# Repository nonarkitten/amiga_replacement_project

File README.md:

# Amiga Replacement Project

_"To make replacements for all the custom chips of the AMIGA, useable in any real AMIGA."_

All documentation is provided for the benefit of the community and the preservation of the original Amiga.

The files herein are presented as a work-in-progress.

ReAgnus as developed by Stephen Leary the patents and any documentation included here for reference and may be considered Public Domain. I claim no licensing on any of these.

ReAgnus developed by the Buffee Project (code named Willoe) is under the <a rel="license" href="http://creativecommons.org/licenses/by-nc-sa/4.0/">Creative Commons Attribution-NonCommercial-ShareAlike 4.0 International License</a>. No part of which shall be used for any commercial gains without express and written permission from The Buffee Project.

This is an attempt to make clean Verilog sources for each chip on the Amiga. Unlike MiniMig and related implementations, this seeks to maintain perfect compatibility with the whole chip and the whole chip only to serve as a second-source to the slowly disappearing stock of Amiga chips. These will be drop-in replacements.

To view the plan of record for each chip, please visit the README.md for each project.

Much of the work is based on the excellent efforts of Dennis van Weeren and Frederic Requin (https://github.com/fredrequin).

## OCS
Our OCS goal will include a 512KB Agnus, Denise and Paula supporting basic NTSC and PAL modes. OCS should be drop-in compatible with the Amiga 1000 "skinny" Agnus as well as the early "fat" Agnus on Amiga 500 and 2000 systems. Eventually we will have a DIP 48 solution for this as well.

## ECS
Expands the chip memory to 2MB with two common pin outs that are slightly incompatible with each other. Some bugs need to be supported but the weird limitations of productivity mode do not. The PLCC socketed PCB for Agnus will present a unique engineering challenge; the other chips remain DIP 48.

## AGA-on-ECS
This provides as much AGA functionality on either OCS or ECS based systems and retains the existing pinouts (and 16-bit data bus limitation). It should be possible to implement FP/EDO memory to get 2X increase and it might be possible to extend that to a 4X improvement with faster memory. We may also simply use SDRAM (3.3V SDR) and start with the fastest memory we can to achieve this.

## Vampire AGA
We'may also add to the AGA core some of the added features of the Vampire.

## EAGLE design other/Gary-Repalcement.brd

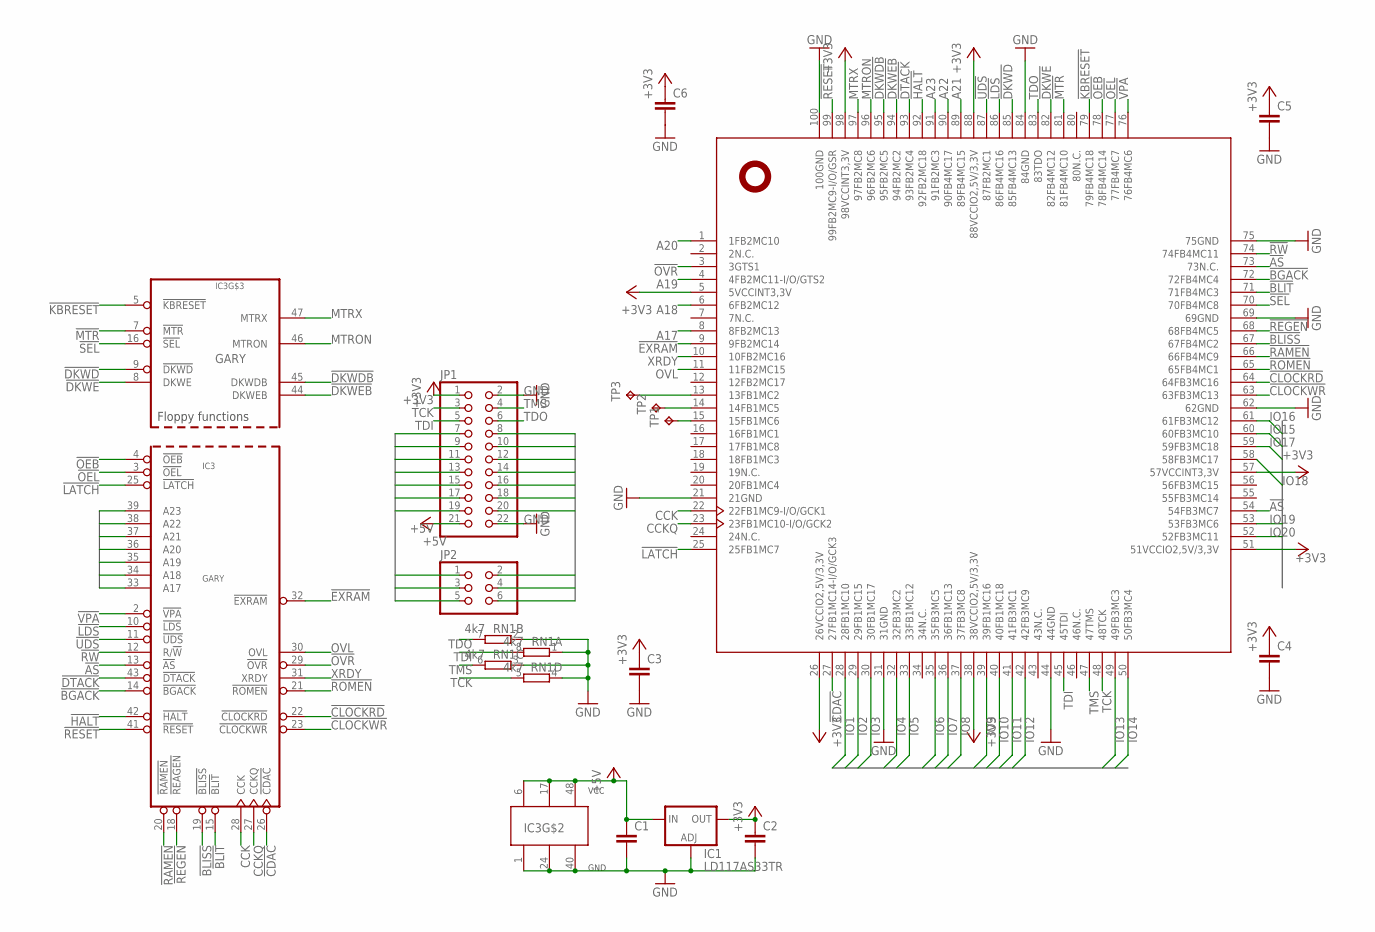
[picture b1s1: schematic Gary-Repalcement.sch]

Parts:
C1, C2: C-EUC0805K; C0805K
C3, C4, C5, C6: C-EUC0603; C0603
IC1: LD117AS33TR; SOT223
IC2: XC9572XLTQ100; TQ100
IC3: GARY_DIP-LABELS; DIP48-GARY
JP1: PINHD-2X11; 2X11
JP2: PINHD-2X3; 2X03
RN1: 4k7; 0603-ARC
TP1, TP2, TP3: TPB1,27; B1,27

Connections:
!AS: IC2.54 (54FB3MC7), IC2.73 (73N.C.), IC3.13 (!AS)
!BGACK: IC2.72 (72FB4MC4), IC3.14 (!BGACK)
!BLISS: IC2.67 (67FB4MC2), IC3.19 (!BLISS)
!BLIT: IC2.71 (71FB4MC3), IC3.15 (!BLIT)
!CDAC: IC2.27 (27FB1MC14-I/O/GCK3), IC3.26 (!CDAC)
!CLOCKRD: IC2.64 (64FB3MC16), IC3.22 (!CLOCKRD)
!CLOCKWR: IC2.63 (63FB3MC13), IC3.23 (!CLOCKWR)
!DKWD: IC2.85 (85FB4MC13), IC3.9 (!DKWD)
!DKWDB: IC2.95 (95FB2MC5), IC3.45 (DKWDB)
!DKWE: IC2.82 (82FB4MC12), IC3.8 (DKWE)
!DKWEB: IC2.94 (94FB2MC2), IC3.44 (DKWEB)
!DTACK: IC2.93 (93FB2MC4), IC3.43 (!DTACK)
!EXRAM: IC2.9 (9FB2MC14), IC3.32 (!EXRAM)
!HALT: IC2.92 (92FB2MC18), IC3.42 (!HALT)
!KBRESET: IC2.79 (79FB4MC18), IC3.5 (!KBRESET)
!LATCH: IC2.25 (25FB1MC7), IC3.25 (!LATCH)
!LDS: IC2.86 (86FB4MC16), IC3.10 (!LDS)
!MTR: IC2.81 (81FB4MC10), IC3.7 (!MTR)
!OEB: IC2.78 (78FB4MC14), IC3.4 (!OEB)
!OEL: IC2.77 (77FB4MC7), IC3.3 (!OEL)
!OVR: IC2.3 (3GTS1), IC3.29 (!OVR)
!RAMEN: IC2.66 (66FB4MC9), IC3.20 (!RAMEN)
!REGEN: IC2.68 (68FB4MC5), IC3.18 (!REAGEN)
!RESET: IC2.99 (99FB2MC9-I/O/GSR), IC3.41 (!RESET)
!ROMEN: IC2.65 (65FB4MC1), IC3.21 (!ROMEN)
!RW: IC2.74 (74FB4MC11), IC3.12 (R/!W!)
!SEL: IC2.70 (70FB4MC8), IC3.16 (!SEL)
!UDS: IC2.87 (87FB2MC1), IC3.11 (!UDS)
!VPA: IC2.76 (76FB4MC6), IC3.2 (!VPA)
+3V3: C2.1, C3.1, C4.1, C5.1, C6.1, IC1.2 (OUT), IC1.4 (OUT), IC2.5 (5VCCINT3,3V), IC2.26 (26VCCIO2,5V/3,3V), IC2.38 (38VCCIO2,5V/3,3V), IC2.51 (51VCCIO2,5V/3,3V), IC2.57 (57VCCINT3,3V), IC2.88 (88VCCIO2,5V/3,3V), IC2.98 (98VCCINT3,3V), JP1.1
+5V: C1.1, IC1.3 (IN), IC3.6 (VCC), IC3.17 (VCC), IC3.48 (VCC), JP1.21
A17: IC2.8 (8FB2MC13), IC3.33 (A17)
A18: IC2.6 (6FB2MC12), IC3.34 (A18)
A19: IC2.4 (4FB2MC11-I/O/GTS2), IC3.35 (A19)
A20: IC2.1 (1FB2MC10), IC3.36 (A20)
A21: IC2.89 (89FB4MC15), IC3.37 (A21)
A22: IC2.90 (90FB4MC17), IC3.38 (A22)
A23: IC2.91 (91FB2MC3), IC3.39 (A23)
CCK: IC2.22 (22FB1MC9-I/O/GCK1), IC3.28 (CCK)
CCKQ: IC2.23 (23FB1MC10-I/O/GCK2), IC3.27 (CCKQ)
GND: C1.2, C2.2, C3.2, C4.2, C5.2, C6.2, IC1.1 (ADJ), IC2.21 (21GND), IC2.31 (31GND), IC2.44 (44GND), IC2.62 (62GND), IC2.69 (69GND), IC2.75 (75GND), IC2.84 (84GND), IC2.100 (100GND), IC3.1 (GND), IC3.24 (GND), IC3.40 (GND), JP1.2, JP1.22, RN1.1, RN1.2 (1), RN1.3 (1), RN1.4 (1)
IO1: IC2.28 (28FB1MC10), JP1.19
IO2: IC2.29 (29FB1MC15), JP1.20
IO3: IC2.30 (30FB1MC17), JP1.17
IO4: IC2.32 (32FB3MC2), JP1.18
IO5: IC2.33 (33FB1MC12), JP1.15
IO6: IC2.35 (35FB3MC5), JP1.16
IO7: IC2.36 (36FB1MC13), JP1.13
IO8: IC2.37 (37FB3MC8), JP1.14
IO9: IC2.39 (39FB1MC16), JP1.11
IO10: IC2.40 (40FB1MC18), JP1.12
IO11: IC2.41 (41FB3MC1), JP1.9
IO12: IC2.42 (42FB3MC9), JP1.10
IO13: IC2.49 (49FB3MC3), JP1.7
IO14: IC2.50 (50FB3MC4), JP1.8
IO15: IC2.60 (60FB3MC10), JP2.2
IO16: IC2.61 (61FB3MC12), JP2.1
IO17: IC2.59 (59FB3MC18), JP2.4
IO18: IC2.58 (58FB3MC17), JP2.3
IO19: IC2.53 (53FB3MC6), JP2.6
IO20: IC2.52 (52FB3MC11), JP2.5
MTRON: IC2.96 (96FB2MC6), IC3.46 (MTRON)
MTRX: IC2.97 (97FB2MC8), IC3.47 (MTRX)
unnamed: IC2.15 (15FB1MC6), TP1.TP
unnamed: IC2.14 (14FB1MC5), TP2.TP
unnamed: IC2.13 (13FB1MC2), TP3.TP
OVL: IC2.11 (11FB2MC15), IC3.30 (OVL)
TCK: IC2.48 (48TCK), JP1.3, RN1.5 (2)
TDI: IC2.45 (45TDI), JP1.5, RN1.8 (2)
TDO: IC2.83 (83TDO), JP1.6, RN1.7 (2)
TMS: IC2.47 (47TMS), JP1.4, RN1.6 (2)
XRDY: IC2.10 (10FB2MC16), IC3.31 (XRDY)

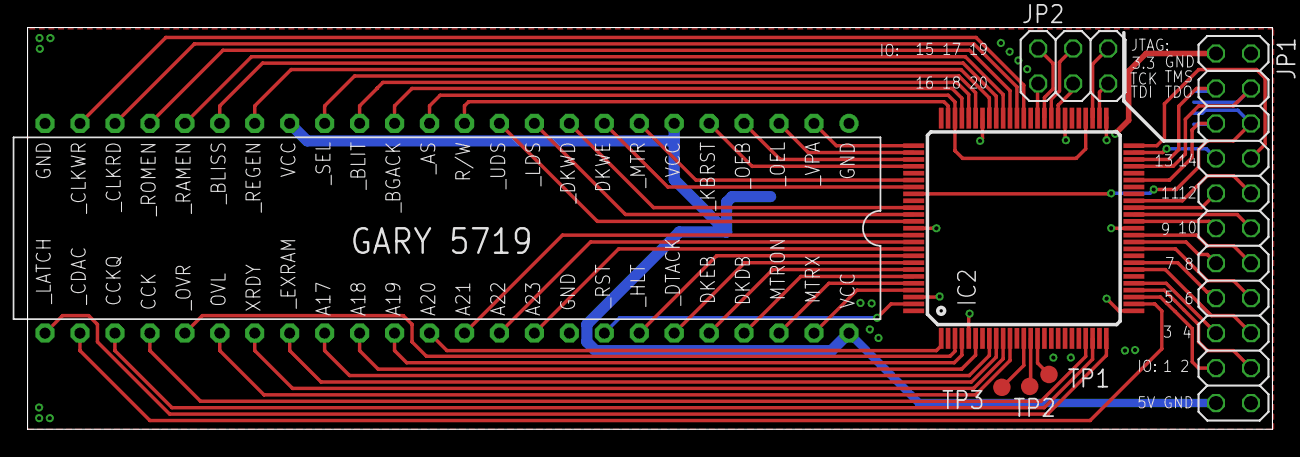
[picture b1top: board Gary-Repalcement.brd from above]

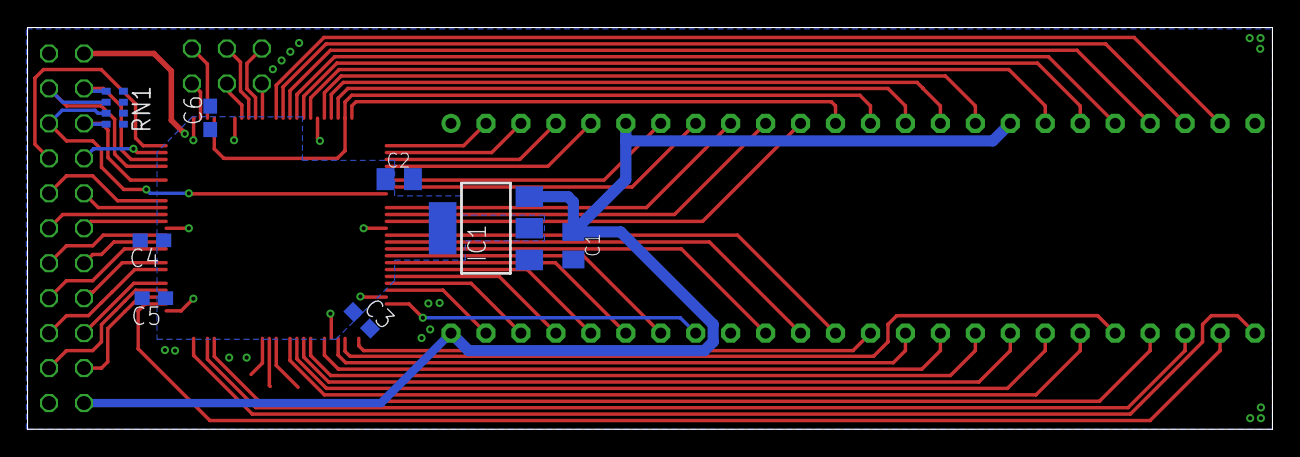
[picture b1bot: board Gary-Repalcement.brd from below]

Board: 2 copper layers, 90.5 x 29.2 mm, 15 parts (8 on the bottom side), 72 nets.

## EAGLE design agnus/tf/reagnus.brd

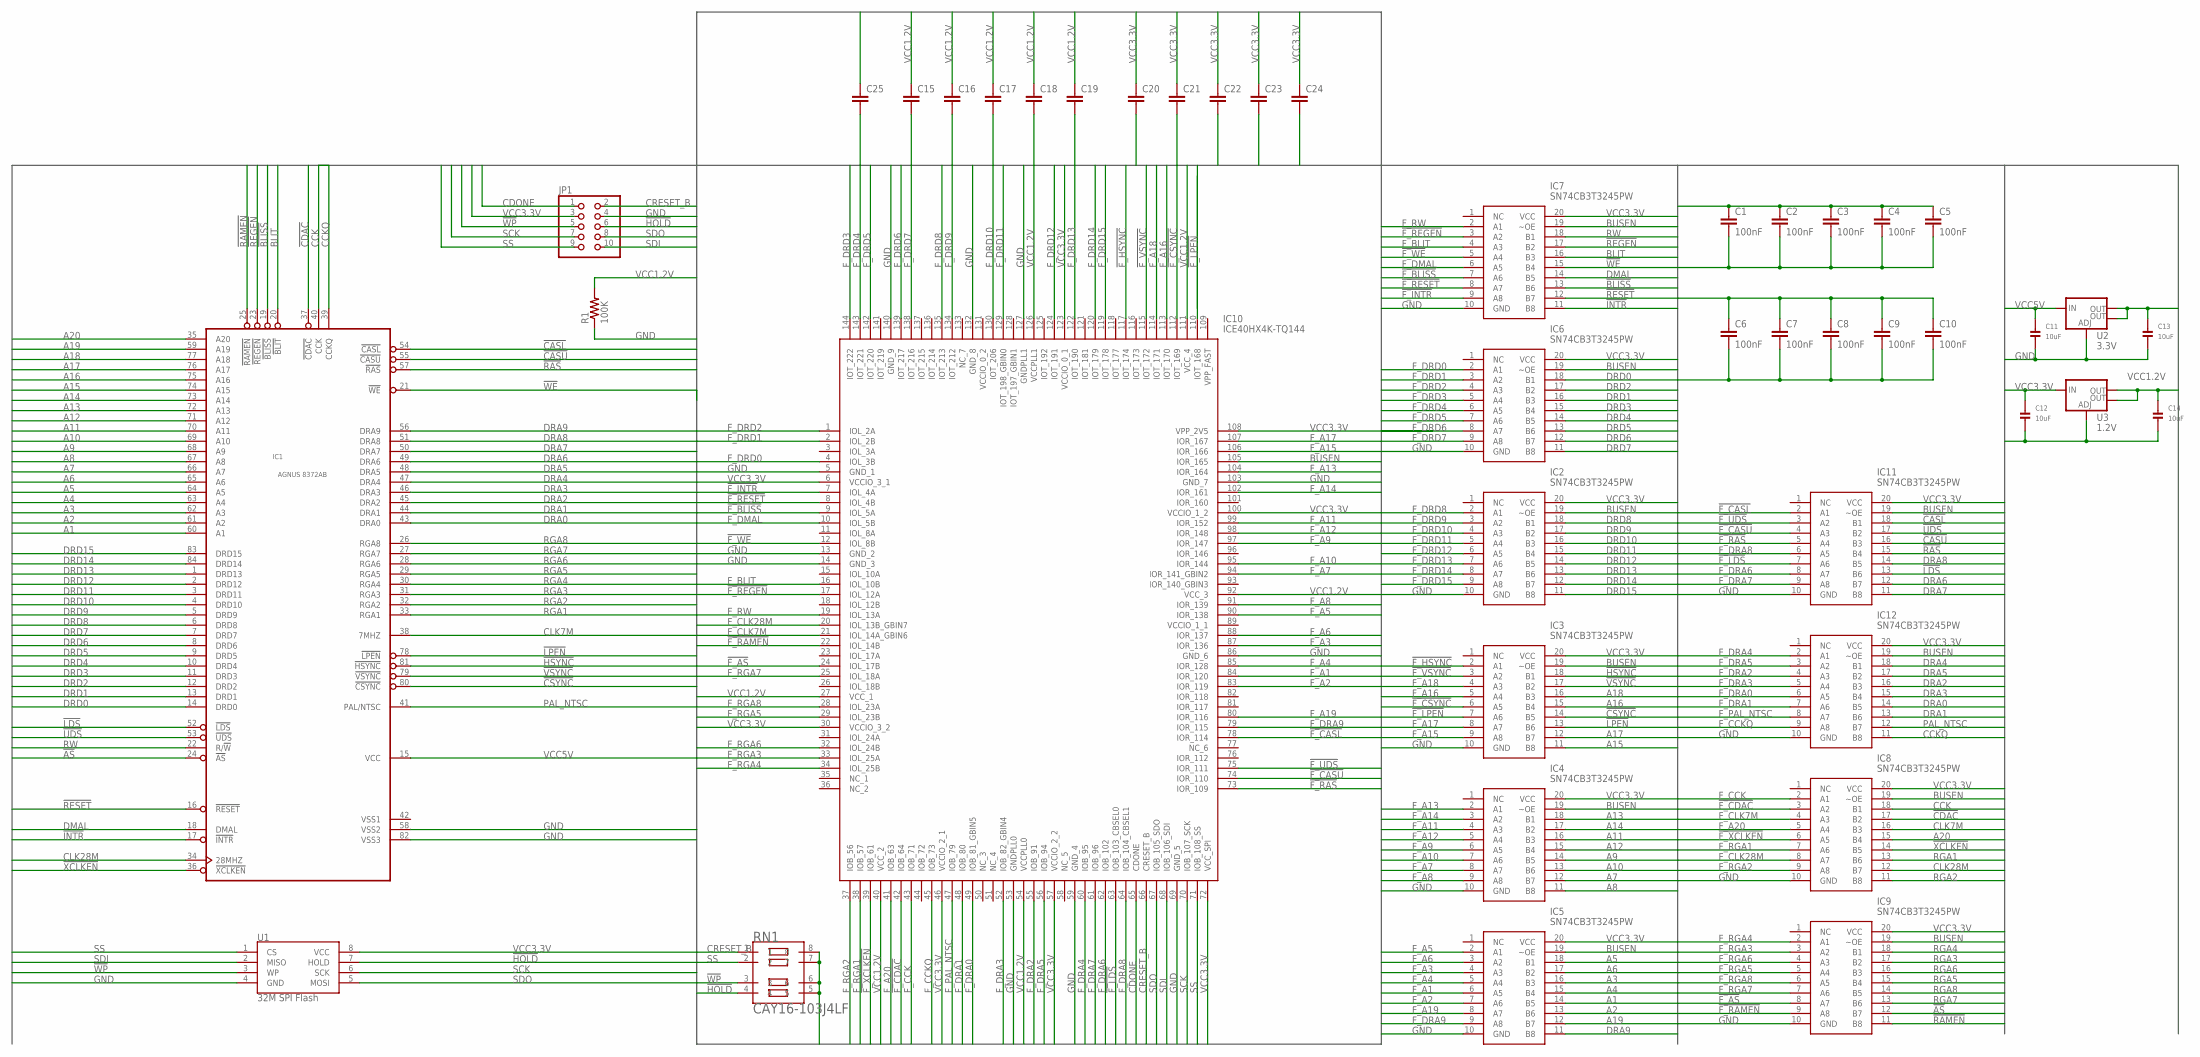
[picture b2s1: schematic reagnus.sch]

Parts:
C1, C2, C3, C4, C5, C6, C7, C8, C9, C10: 100nF; C0805K
C11, C12, C13, C14: 10uF; 1206
C15, C16, C17, C18, C19, C20, C21, C22, C23, C24, C25: C-EUC0805K; C0805K
IC1: AGNUS_8372AB_THT; PLCC84_T
IC2, IC3, IC4, IC5, IC6, IC7, IC8, IC9, IC11, IC12: SN74CB3T3245PW; SOP65P640X120-20N
IC10: ICE40HX4K-TQ144; QFP50P2200X2200X160-144N
JP1: HEADER-2X5; 2X05
R1: 100K; R0805
RN1: CAY16-103J4LF; RESCAXE80P320X160-8N
U1: 32M SPI Flash; SO08
U2: 3.3V; SOT223
U3: 1.2V; SOT223

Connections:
!AS: IC1.24 (!AS), IC9.12 (B7)
!BLISS: IC1.19 (!BLISS), IC7.13 (B6)
!CASL: IC1.54 (!CASL), IC11.18 (B1)
!CASU: IC1.55 (!CASU), IC11.16 (B3)
!CDAC: IC1.37 (!CDAC), IC8.17 (B2)
!CSYNC: IC1.80 (!CSYNC), IC3.14 (B5)
!F_AS: IC9.8 (A7), IC10.24 (IOL_17B)
!F_BLISS: IC7.7 (A6), IC10.9 (IOL_5A)
!F_CASL: IC10.78 (IOR_114), IC11.2 (A1)
!F_CASU: IC10.74 (IOR_110), IC11.4 (A3)
!F_CDAC: IC8.3 (A2), IC10.42 (IOB_64)
!F_CSYNC: IC3.6 (A5), IC10.112 (IOT_169)
!F_HSYNC: IC3.2 (A1), IC10.117 (IOT_174)
!F_INTR: IC7.9 (A8), IC10.7 (IOL_4A)
!F_LDS: IC10.63 (IOB_103_CBSEL0), IC11.7 (A6)
!F_LPEN: IC3.7 (A6), IC10.110 (IOT_168)
!F_RAMEN: IC9.9 (A8), IC10.22 (IOL_14B)
!F_RAS: IC10.73 (IOR_109), IC11.5 (A4)
!F_REGEN: IC7.3 (A2), IC10.17 (IOL_12A)
!F_RESET: IC7.8 (A7), IC10.8 (IOL_4B)
!F_UDS: IC10.75 (IOR_111), IC11.3 (A2)
!F_VSYNC: IC3.3 (A2), IC10.115 (IOT_172)
!F_WE: IC7.5 (A4), IC10.12 (IOL_8B)
!F_XCLKEN: IC8.6 (A5), IC10.39 (IOB_61)
!HOLD: JP1.6, RN1.4, U1.7 (HOLD)
!HSYNC: IC1.81 (!HSYNC), IC3.18 (B1)
!INTR: IC1.17 (!INTR), IC7.11 (B8)
!LDS: IC1.52 (!LDS), IC11.13 (B6)
!LPEN: IC1.78 (!LPEN), IC3.13 (B6)
!RAMEN: IC1.25 (!RAMEN), IC9.11 (B8)
!RAS: IC1.57 (!RAS), IC11.15 (B4)
!REGEN: IC1.23 (!REGEN), IC7.17 (B2)
!RESET: IC1.16 (!RESET), IC7.12 (B7)
!UDS: IC1.53 (!UDS), IC11.17 (B2)
!VSYNC: IC1.79 (!VSYNC), IC3.17 (B2)
!WE: IC1.21 (!WE), IC7.15 (B4)
!WP: JP1.5, RN1.3, U1.3 (WP)
!XCLKEN: IC1.36 (!XCLKEN), IC8.14 (B5)
A1: IC1.60 (A1), IC5.14 (B5)
A2: IC1.61 (A2), IC5.13 (B6)
A3: IC1.62 (A3), IC5.16 (B3)
A4: IC1.63 (A4), IC5.15 (B4)
A5: IC1.64 (A5), IC5.18 (B1)
A6: IC1.65 (A6), IC5.17 (B2)
A7: IC1.66 (A7), IC4.12 (B7)
A8: IC1.67 (A8), IC4.11 (B8)
A9: IC1.68 (A9), IC4.14 (B5)
A10: IC1.69 (A10), IC4.13 (B6)
A11: IC1.70 (A11), IC4.16 (B3)
A12: IC1.71 (A12), IC4.15 (B4)
A13: IC1.72 (A13), IC4.18 (B1)
A14: IC1.73 (A14), IC4.17 (B2)
A15: IC1.74 (A15), IC3.11 (B8)
A16: IC1.75 (A16), IC3.15 (B4)
A17: IC1.76 (A17), IC3.12 (B7)
A18: IC1.77 (A18), IC3.16 (B3)
A19: IC1.59 (A19), IC5.12 (B7)
A20: IC1.35 (A20), IC8.15 (B4)
BLIT: IC1.20 (!BLIT), IC7.16 (B3)
BUSEN: IC2.19 (~OE), IC3.19 (~OE), IC4.19 (~OE), IC5.19 (~OE), IC6.19 (~OE), IC7.19 (~OE), IC8.19 (~OE), IC9.19 (~OE), IC10.105 (IOR_165), IC11.19 (~OE), IC12.19 (~OE)
CCK: IC1.40 (CCK), IC8.18 (B1)
CCKQ: IC1.39 (CCKQ), IC12.11 (B8)
CDONE: IC10.65 (CDONE), JP1.1
CLK7M: IC1.38 (7MHZ), IC8.16 (B3)
CLK28M: IC1.34 (28MHZ), IC8.12 (B7)
CRESET_B: IC10.66 (CRESET_B), JP1.2, RN1.1
DMAL: IC1.18 (DMAL), IC7.14 (B5)
DRA0: IC1.43 (DRA0), IC12.14 (B5)
DRA1: IC1.44 (DRA1), IC12.13 (B6)
DRA2: IC1.45 (DRA2), IC12.16 (B3)
DRA3: IC1.46 (DRA3), IC12.15 (B4)
DRA4: IC1.47 (DRA4), IC12.18 (B1)
DRA5: IC1.48 (DRA5), IC12.17 (B2)
DRA6: IC1.49 (DRA6), IC11.12 (B7)
DRA7: IC1.50 (DRA7), IC11.11 (B8)
DRA8: IC1.51 (DRA8), IC11.14 (B5)
DRA9: IC1.56 (DRA9), IC5.11 (B8)
DRD0: IC1.14 (DRD0), IC6.18 (B1)
DRD1: IC1.13 (DRD1), IC6.16 (B3)
DRD2: IC1.12 (DRD2), IC6.17 (B2)
DRD3: IC1.11 (DRD3), IC6.15 (B4)
DRD4: IC1.10 (DRD4), IC6.14 (B5)
DRD5: IC1.9 (DRD5), IC6.13 (B6)
DRD6: IC1.8 (DRD6), IC6.12 (B7)
DRD7: IC1.7 (DRD7), IC6.11 (B8)
DRD8: IC1.6 (DRD8), IC2.18 (B1)
DRD9: IC1.5 (DRD9), IC2.17 (B2)
DRD10: IC1.4 (DRD10), IC2.16 (B3)
DRD11: IC1.3 (DRD11), IC2.15 (B4)
DRD12: IC1.2 (DRD12), IC2.14 (B5)
DRD13: IC1.1 (DRD13), IC2.13 (B6)
DRD14: IC1.84 (DRD14), IC2.12 (B7)
DRD15: IC1.83 (DRD15), IC2.11 (B8)
F_A1: IC5.6 (A5), IC10.84 (IOR_120)
F_A2: IC5.7 (A6), IC10.83 (IOR_119)
F_A3: IC5.4 (A3), IC10.87 (IOR_136)
F_A4: IC5.5 (A4), IC10.85 (IOR_128)
F_A5: IC5.2 (A1), IC10.90 (IOR_138)
F_A6: IC5.3 (A2), IC10.88 (IOR_137)
F_A7: IC4.8 (A7), IC10.94 (IOR_141_GBIN2)
F_A8: IC4.9 (A8), IC10.91 (IOR_139)
F_A9: IC4.6 (A5), IC10.97 (IOR_147)
F_A10: IC4.7 (A6), IC10.95 (IOR_144)
F_A11: IC4.4 (A3), IC10.99 (IOR_152)
F_A12: IC4.5 (A4), IC10.98 (IOR_148)
F_A13: IC4.2 (A1), IC10.104 (IOR_164)
F_A14: IC4.3 (A2), IC10.102 (IOR_161)
F_A15: IC3.9 (A8), IC10.106 (IOR_166)
F_A16: IC3.5 (A4), IC10.113 (IOT_170)
F_A17: IC3.8 (A7), IC10.107 (IOR_167)
F_A18: IC3.4 (A3), IC10.114 (IOT_171)
F_A19: IC5.8 (A7), IC10.80 (IOR_116)
F_A20: IC8.5 (A4), IC10.41 (IOB_63)
F_BLIT: IC7.4 (A3), IC10.16 (IOL_10B)
F_CCK: IC8.2 (A1), IC10.43 (IOB_71)
F_CCKQ: IC10.45 (IOB_73), IC12.9 (A8)
F_CLK7M: IC8.4 (A3), IC10.21 (IOL_14A_GBIN6)
F_CLK28M: IC8.8 (A7), IC10.20 (IOL_13B_GBIN7)
F_DMAL: IC7.6 (A5), IC10.10 (IOL_5B)
F_DRA0: IC10.49 (IOB_81_GBIN5), IC12.6 (A5)
F_DRA1: IC10.48 (IOB_80), IC12.7 (A6)
F_DRA2: IC10.55 (IOB_91), IC12.4 (A3)
F_DRA3: IC10.52 (IOB_82_GBIN4), IC12.5 (A4)
F_DRA4: IC10.60 (IOB_95), IC12.2 (A1)
F_DRA5: IC10.56 (IOB_94), IC12.3 (A2)
F_DRA6: IC10.62 (IOB_102), IC11.8 (A7)
F_DRA7: IC10.61 (IOB_96), IC11.9 (A8)
F_DRA8: IC10.64 (IOB_104_CBSEL1), IC11.6 (A5)
F_DRA9: IC5.9 (A8), IC10.79 (IOR_115)
F_DRD0: IC6.2 (A1), IC10.4 (IOL_3B)
F_DRD1: IC6.3 (A2), IC10.2 (IOL_2B)
F_DRD2: IC6.4 (A3), IC10.1 (IOL_2A)
F_DRD3: IC6.5 (A4), IC10.144 (IOT_222)
F_DRD4: IC6.6 (A5), IC10.143 (IOT_221)
F_DRD5: IC6.7 (A6), IC10.142 (IOT_220)
F_DRD6: IC6.8 (A7), IC10.139 (IOT_217)
F_DRD7: IC6.9 (A8), IC10.138 (IOT_216)
F_DRD8: IC2.2 (A1), IC10.135 (IOT_213)
F_DRD9: IC2.3 (A2), IC10.134 (IOT_212)
F_DRD10: IC2.4 (A3), IC10.130 (IOT_206)
F_DRD11: IC2.5 (A4), IC10.129 (IOT_198_GBIN0)
F_DRD12: IC2.6 (A5), IC10.124 (IOT_191)
F_DRD13: IC2.7 (A6), IC10.122 (IOT_190)
F_DRD14: IC2.8 (A7), IC10.120 (IOT_179)
F_DRD15: IC2.9 (A8), IC10.119 (IOT_178)
F_PAL_NTSC: IC10.47 (IOB_79), IC12.8 (A7)
F_RGA1: IC8.7 (A6), IC10.38 (IOB_57)
F_RGA2: IC8.9 (A8), IC10.37 (IOB_56)
F_RGA3: IC9.3 (A2), IC10.33 (IOL_25A)
F_RGA4: IC9.2 (A1), IC10.34 (IOL_25B)
F_RGA5: IC9.5 (A4), IC10.29 (IOL_23B)
F_RGA6: IC9.4 (A3), IC10.32 (IOL_24B)
F_RGA7: IC9.7 (A6), IC10.25 (IOL_18A)
F_RGA8: IC9.6 (A5), IC10.28 (IOL_23A)
F_RW: IC7.2 (A1), IC10.19 (IOL_13A)
GND: C1.2, C2.2, C3.2, C4.2, C5.2, C6.2, C7.2, C8.2, C9.2, C10.2, C11.2, C12.2, C13.2, C14.2, C15.2, C16.2, C17.2, C18.2, C19.2, C20.2, C21.2, C22.2, C23.2, C24.2, C25.2, IC1.58 (VSS2), IC1.82 (VSS3), IC2.10 (GND), IC3.10 (GND), IC4.10 (GND), IC5.10 (GND), IC6.10 (GND), IC7.10 (GND), IC8.10 (GND), IC9.10 (GND), IC10.5 (GND_1), IC10.13 (GND_2), IC10.14 (GND_3), IC10.53 (GNDPLL0), IC10.59 (GND_4), IC10.69 (GND_5), IC10.86 (GND_6), IC10.103 (GND_7), IC10.127 (GNDPLL1), IC10.132 (GND_8), IC10.140 (GND_9), IC11.10 (GND), IC12.10 (GND), JP1.4, R1.1, U1.4 (GND), U2.1 (ADJ), U3.1 (ADJ)
PAL_NTSC: IC1.41 (PAL/NTSC), IC12.12 (B7)
RGA1: IC1.33 (RGA1), IC8.13 (B6)
RGA2: IC1.32 (RGA2), IC8.11 (B8)
RGA3: IC1.31 (RGA3), IC9.17 (B2)
RGA4: IC1.30 (RGA4), IC9.18 (B1)
RGA5: IC1.29 (RGA5), IC9.15 (B4)
RGA6: IC1.28 (RGA6), IC9.16 (B3)
RGA7: IC1.27 (RGA7), IC9.13 (B6)
RGA8: IC1.26 (RGA8), IC9.14 (B5)
RW: IC1.22 (R/!W!), IC7.18 (B1)
SCK: IC10.70 (IOB_107_SCK), JP1.7, U1.6 (SCK)
SDI: IC10.68 (IOB_106_SDI), JP1.10, U1.2 (MISO)
SDO: IC10.67 (IOB_105_SDO), JP1.8, U1.5 (MOSI)
SS: IC10.71 (IOB_108_SS), JP1.9, RN1.2, U1.1 (CS)
VCC1.2V: C14.1, C15.1, C16.1, C17.1, C18.1, C19.1, C25.1, IC10.27 (VCC_1), IC10.40 (VCC_2), IC10.54 (VCCPLL0), IC10.92 (VCC_3), IC10.111 (VCC_4), IC10.126 (VCCPLL1), R1.2, U3.2 (OUT), U3.4 (OUT)
VCC3.3V: C1.1, C2.1, C3.1, C4.1, C5.1, C6.1, C7.1, C8.1, C9.1, C10.1, C12.1, C13.1, C20.1, C21.1, C22.1, C23.1, C24.1, IC2.20 (VCC), IC3.20 (VCC), IC4.20 (VCC), IC5.20 (VCC), IC6.20 (VCC), IC7.20 (VCC), IC8.20 (VCC), IC9.20 (VCC), IC10.6 (VCCIO_3_1), IC10.30 (VCCIO_3_2), IC10.46 (VCCIO_2_1), IC10.57 (VCCIO_2_2), IC10.72 (VCC_SPI), IC10.100 (VCCIO_1_2), IC10.108 (VPP_2V5), IC10.123 (VCCIO_0_1), IC11.20 (VCC), IC12.20 (VCC), JP1.3, RN1.5, RN1.6, RN1.7, RN1.8, U1.8 (VCC), U2.2 (OUT), U2.4 (OUT), U3.3 (IN)
VCC5V: C11.1, IC1.15 (VCC), U2.3 (IN)
VSS1: IC1.42 (VSS1)

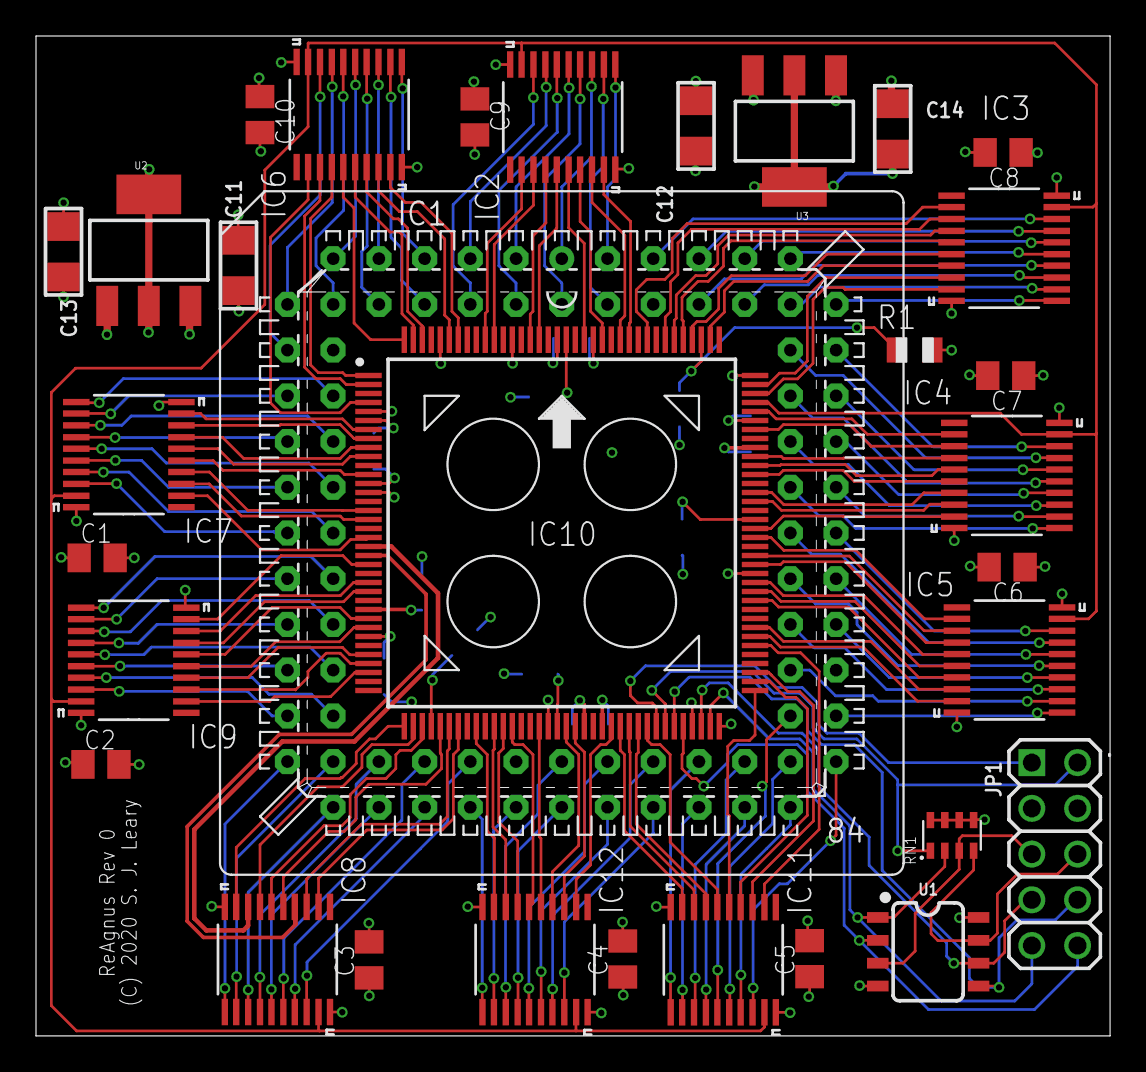
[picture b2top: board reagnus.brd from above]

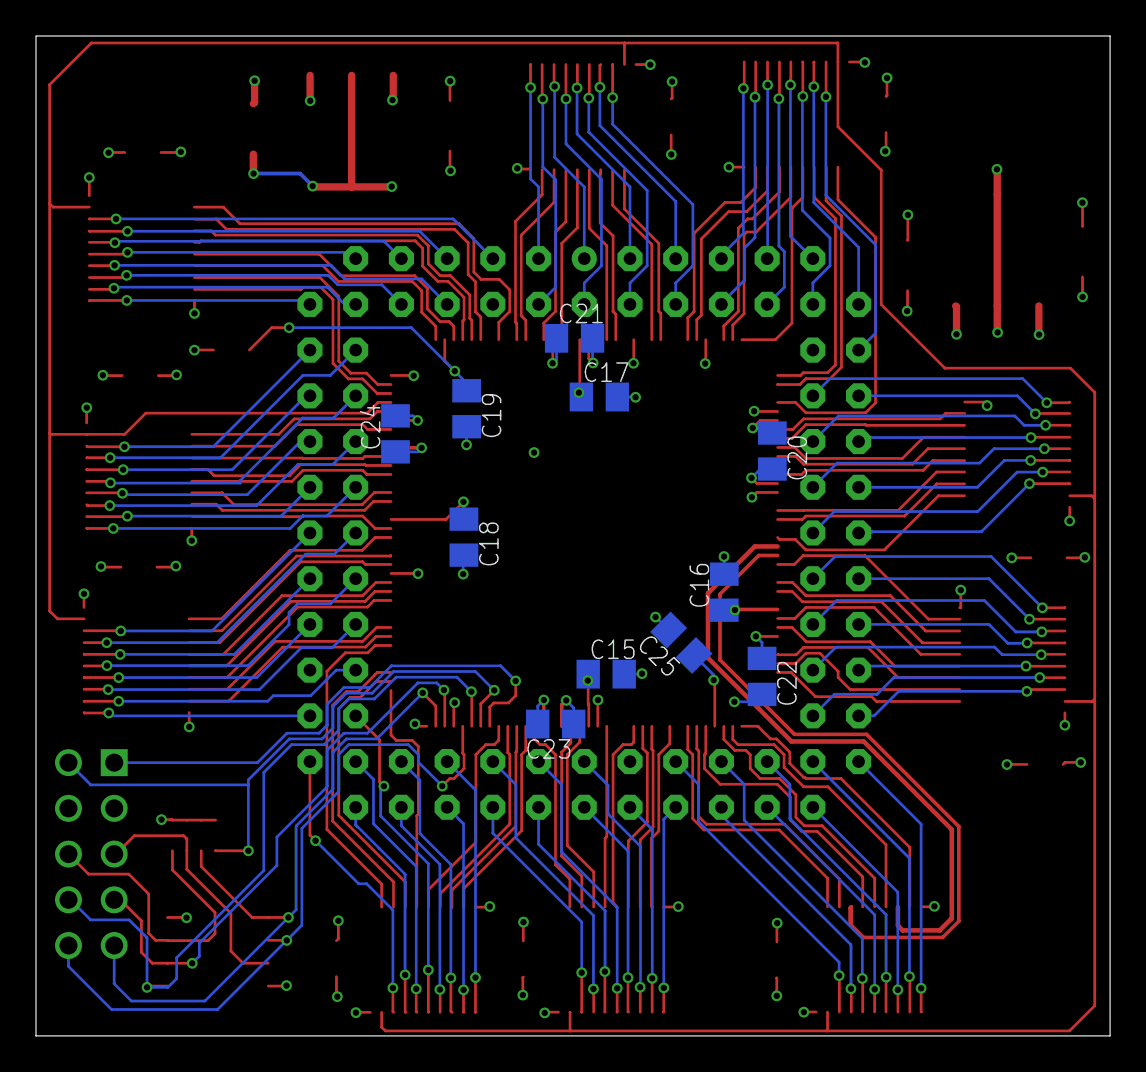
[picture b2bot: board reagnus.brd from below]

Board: 4 copper layers, 59.7 x 55.5 mm, 43 parts (11 on the bottom side), 173 nets.

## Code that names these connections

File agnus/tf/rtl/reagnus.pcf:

# Copyright (C) 2020, Stephen J. Leary
# All rights reserved.
#
# This file is part of ReAgnus
#
# ReAgnus is free software: you can redistribute it and/or modify
# it under the terms of the GNU General Public License as published by
# the Free Software Foundation, either version 3 of the License, or
# (at your option) any later version.
#
# ReAgnus is distributed in the hope that it will be useful,
# but WITHOUT ANY WARRANTY; without even the implied warranty of
# MERCHANTABILITY or FITNESS FOR A PARTICULAR PURPOSE.  See the
# GNU General Public License for more details.
#
# You should have received a copy of the GNU General Public License
# along with ReAgnus. If not, see <http://www.gnu.org/licenses/>.

set_io --warn-no-port AS_N 24
set_io --warn-no-port BLISS_N 9
set_io --warn-no-port CASL_N 78
set_io --warn-no-port CASU_N 74
set_io --warn-no-port CDAC_N 42
set_io --warn-no-port CSYNC_N 112
set_io --warn-no-port HSYNC_N 117
set_io --warn-no-port INTR_N 7
set_io --warn-no-port LDS_N 63
set_io --warn-no-port LPEN_N 110
set_io --warn-no-port RAMEN_N 22
set_io --warn-no-port RAS_N 73
set_io --warn-no-port REGEN_N 17
set_io --warn-no-port RESET_N 8
set_io --warn-no-port UDS_N 75
set_io --warn-no-port VSYNC_N 115
set_io --warn-no-port WE_N 12
set_io --warn-no-port XCLKEN_N 39
set_io --warn-no-port BUSEN 105
set_io --warn-no-port A<1> 84
set_io --warn-no-port A<2> 83
set_io --warn-no-port A<3> 87
set_io --warn-no-port A<4> 85
set_io --warn-no-port A<5> 90
set_io --warn-no-port A<6> 88
set_io --warn-no-port A<7> 94
set_io --warn-no-port A<8> 91
set_io --warn-no-port A<9> 97
set_io --warn-no-port A<10> 95
set_io --warn-no-port A<11> 99
set_io --warn-no-port A<12> 98
set_io --warn-no-port A<13> 104
set_io --warn-no-port A<14> 102
set_io --warn-no-port A<15> 106
set_io --warn-no-port A<16> 113
set_io --warn-no-port A<17> 107
set_io --warn-no-port A<18> 114
set_io --warn-no-port A<19> 80
set_io --warn-no-port A<20> 41
set_io --warn-no-port BLIT 16
set_io --warn-no-port CCK 43
set_io --warn-no-port CCKQ 45
set_io --warn-no-port CLK7M 21
set_io --warn-no-port CLK28M 20
set_io --warn-no-port DMAL 10
set_io --warn-no-port DRA<0> 49
set_io --warn-no-port DRA<1> 48
set_io --warn-no-port DRA<2> 55
set_io --warn-no-port DRA<3> 52
set_io --warn-no-port DRA<4> 60
set_io --warn-no-port DRA<5> 56
set_io --warn-no-port DRA<6> 62
set_io --warn-no-port DRA<7> 61
set_io --warn-no-port DRA<8> 64
set_io --warn-no-port DRA<9> 79
set_io --warn-no-port DRD<0> 4
set_io --warn-no-port DRD<1> 2
set_io --warn-no-port DRD<2> 1
set_io --warn-no-port DRD<3> 144
set_io --warn-no-port DRD<4> 143
set_io --warn-no-port DRD<5> 142
set_io --warn-no-port DRD<6> 139
set_io --warn-no-port DRD<7> 138
set_io --warn-no-port DRD<8> 135
set_io --warn-no-port DRD<9> 134
set_io --warn-no-port DRD<10> 130
set_io --warn-no-port DRD<11> 129
set_io --warn-no-port DRD<12> 124
set_io --warn-no-port DRD<13> 122
set_io --warn-no-port DRD<14> 120
set_io --warn-no-port DRD<15> 119
set_io --warn-no-port PAL_NTSC 47
set_io --warn-no-port RGA<1> 38
set_io --warn-no-port RGA<2> 37
set_io --warn-no-port RGA<3> 33
set_io --warn-no-port RGA<4> 34
set_io --warn-no-port RGA<5> 29
set_io --warn-no-port RGA<6> 32
set_io --warn-no-port RGA<7> 25
set_io --warn-no-port RGA<8> 28
set_io --warn-no-port RW 19

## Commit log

2020-02-20 Create place_holder
2020-03-12 Update Denise.v
    Verified clocks against Amiga 500+ Technical Reference Manual
2020-03-15 Rename Agnus.v to agnus/Agnus.v
2020-03-15 Rename Denise.v to denise/Denise.v
2020-03-15 Rename denise_top.v to denise/denise_top.v
2020-03-15 Rename Denise.v to denise/Denise.v (#1)
    * Rename Denise.v to denise/Denise.v
    * Rename denise_top.v to denise/denise_top.v
2020-03-15 Rename Paula.v to paula/Paula.v
2020-03-15 Rename dma_cache.v to agnus/dma_cache.v
2020-03-15 Rename sdram_ctrl.v to agnus/sdram_ctrl.v
2020-03-15 Rename Paula.v to paula/Paula.v (#2)
    * Rename Paula.v to paula/Paula.v
    * Rename dma_cache.v to agnus/dma_cache.v
    * Rename sdram_ctrl.v to agnus/sdram_ctrl.v
2022-08-13 added AA-chipset specs pdf
2022-08-13 added Agnus and Alice chipset specs pdfs
2022-08-13 added Fat-Gary chip spec pdf
2022-08-13 added a more readable Gayle chip spec pdf
2022-08-13 added Lisa chip spec pdf
2022-08-13 added Ramsey chip spec pdf
2022-08-13 added D.Haynie US5276887-patent, about bus arbitration system for granting bus access to devices.
2022-08-13 added Denise chip spec pdf
2022-08-17 More docs (#8)
    * added AA-chipset specs pdf
    * added Agnus and Alice chipset specs pdfs
    * added Fat-Gary chip spec pdf
    * added a more readable Gayle chip spec pdf
    * added Lisa chip spec pdf
    * added Ramsey chip spec pdf
2022-08-17 Nonarkitten patch 1 (#9)
    * Added Stephen Leary's ReAgnus as sent to me
    * Added preliminary info on Willoe (my own "ReAgnus")
2022-08-23 Update Paula.v
    Minor typos, actually compile now.
2022-08-26 Nonarkitten patch 1 (#10)
    * Create empty.txt
    * Add files via upload
    * Create README.md
2022-09-22 Added Gayle Rev5 schematics
2022-09-22 Added CIA specs
2023-02-03 For utri007
2023-03-22 Moving to common folder
2023-03-22 Create empty.txt (#13)
    * Create empty.txt
    * Add files via upload
    * Moving to common folder
2023-03-24 Add christians latest (#14)
    * Added Gayle Rev5 schematics
    * Added CIA specs
    * Create empty.txt
    * Add files via upload
    * Moving to common folder
    ---------
2023-03-24 Nonarkitten patch 1 (#15)
    * Create empty.txt
    * Add files via upload
    * Moving to common folder
2023-03-24 Clean up duplicates, moved GAYLE chip spec to gayle folder
2023-04-10 Update edits to MiniMig
2023-04-10 Added new mixer
2023-08-08 Update Paula.v
    Fixes issue #16 IPL outputs are now Z in place of high.
2024-04-05 Add files
2024-04-27 more docs (#18)
    * Add files via upload
    * Add files
    * Add files via upload
2025-01-13 Fat Ramsey Internal schematics
2025-01-13 Fat Ramsey Internal schematics (#20)
2025-02-09 moved and rename Gary_specification.pdf to FatGary folder
2025-02-09 added Fat Gary schematics
2025-02-09 Created separate folder for fat gary and added the schematics and spec files to it. (#21)
    * Fat Ramsey Internal schematics
    * moved and rename Gary_specification.pdf to FatGary folder
    * added Fat Gary schematics
2026-01-21 Adds CIA implentation with associated testbench
2026-01-22 Invert timer logic.
    This allows to use '0' as internal default value since 'initial' blocks may not be applied by fpga synthesis tools.
    This way, the CIA is properly initialized when powering up
2026-01-24 fix icr_rst typo and use reduce and for fast mode
2026-02-03 Merge CIA 8520 (#31)
    * Adds CIA implentation with associated testbench
    * Invert timer logic.
    This allows to use '0' as internal default value since 'initial' blocks may not be applied by fpga synthesis tools.
    This way, the CIA is properly initialized when powering up
    * fix icr_rst typo and use reduce and for fast mode
    ---------
2026-02-03 Replace previous CIA 8520 core with new modular implementation
    - disabled CIA extensions and make them configurable
    - splitted logic into smaller submodules
    - refectored decoder to use less logic
    - refactored serial shifting
    - fixed some timing bugs
    - added more tests
2026-02-03 Fix typo in filename
2026-02-03 Replace previous CIA 8520 core with new modular implementation (#32)
    * Replace previous CIA 8520 core with new modular implementation
    - disabled CIA extensions and make them configurable
    - splitted logic into smaller submodules
    - refectored decoder to use less logic
    - refactored serial shifting
    - fixed some timing bugs
2026-03-05 Updated production files for Denise
2026-03-07 WIP, need to commit to try something else
2026-04-08 Added Lisa Schematics & initial verilog for bitplane
2026-04-15 Fixed up clocks, cdc back in, hpos matched schematics
2026-04-15 Change cfg to parameters.
2026-04-21 Corected clock and moved out of top
2026-04-21 Minor cleanup with naming
2026-04-21 Added WENx and programmable blank
2026-04-21 Added AGA cfg, added some AGA regs, fixed composite blanking

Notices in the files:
README.md:
CC BY-NC-SA 4.0
agnus/tf/reagnus.brd:
(C) 2020 S. J. Leary
parts and their libraries:
SparkFun-IC-Memory: Licensing: Creative Commons ShareAlike 4.0 International - https://creativecommons.org/licenses/by-sa/4.0
microbuilder: This work is placed in the public domain, and may be freely used for commercial and non-commercial work with the following conditions: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
